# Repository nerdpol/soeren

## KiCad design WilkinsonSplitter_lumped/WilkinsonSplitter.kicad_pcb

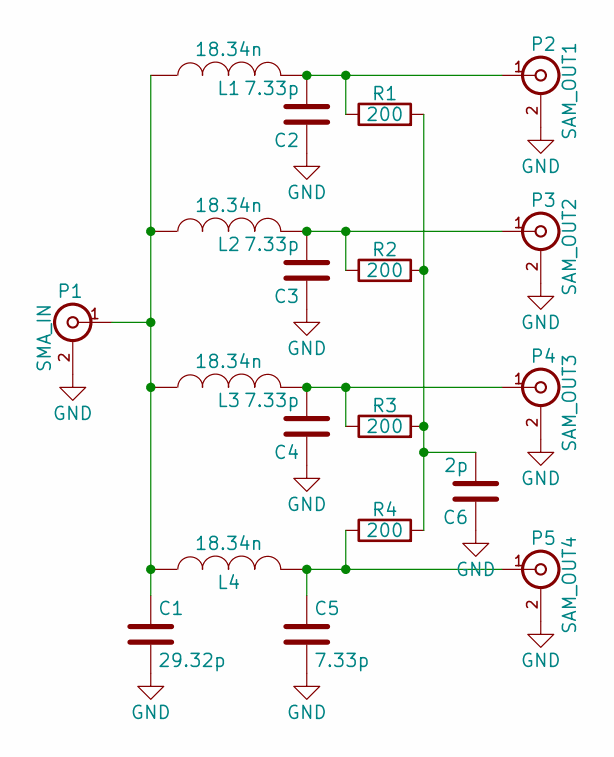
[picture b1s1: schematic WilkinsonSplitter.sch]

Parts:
C1: 29.32p; C_0402
C2, C3, C4, C5: 7.33p; C_0402
C6: 2p; C_0402
L1, L2, L3, L4: 18.34n; C_0402
P1: SMA_IN; Molex_SMA_Jack_Edge_Mount
P2: SAM_OUT1; Molex_SMA_Jack_Edge_Mount
P3: SAM_OUT2; Molex_SMA_Jack_Edge_Mount
P4: SAM_OUT3; Molex_SMA_Jack_Edge_Mount
P5: SAM_OUT4; Molex_SMA_Jack_Edge_Mount
R1, R2, R3, R4: 200; R_0402

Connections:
GND: C1.2, C2.1, C3.1, C4.1, C5.2, C6.1, P1.2 (Ext), P2.2 (Ext), P3.2 (Ext), P4.2 (Ext), P5.2 (Ext)
unnamed: C1.1, L1.1, L2.1, L3.1, L4.1, P1.1 (In)
unnamed: C2.2, L1.2, P2.1 (In), R1.1
unnamed: C3.2, L2.2, P3.1 (In), R2.1
unnamed: C4.2, L3.2, P4.1 (In), R3.1
unnamed: C5.1, L4.2, P5.1 (In), R4.1
unnamed: C6.2, R1.2, R2.2, R3.2, R4.2

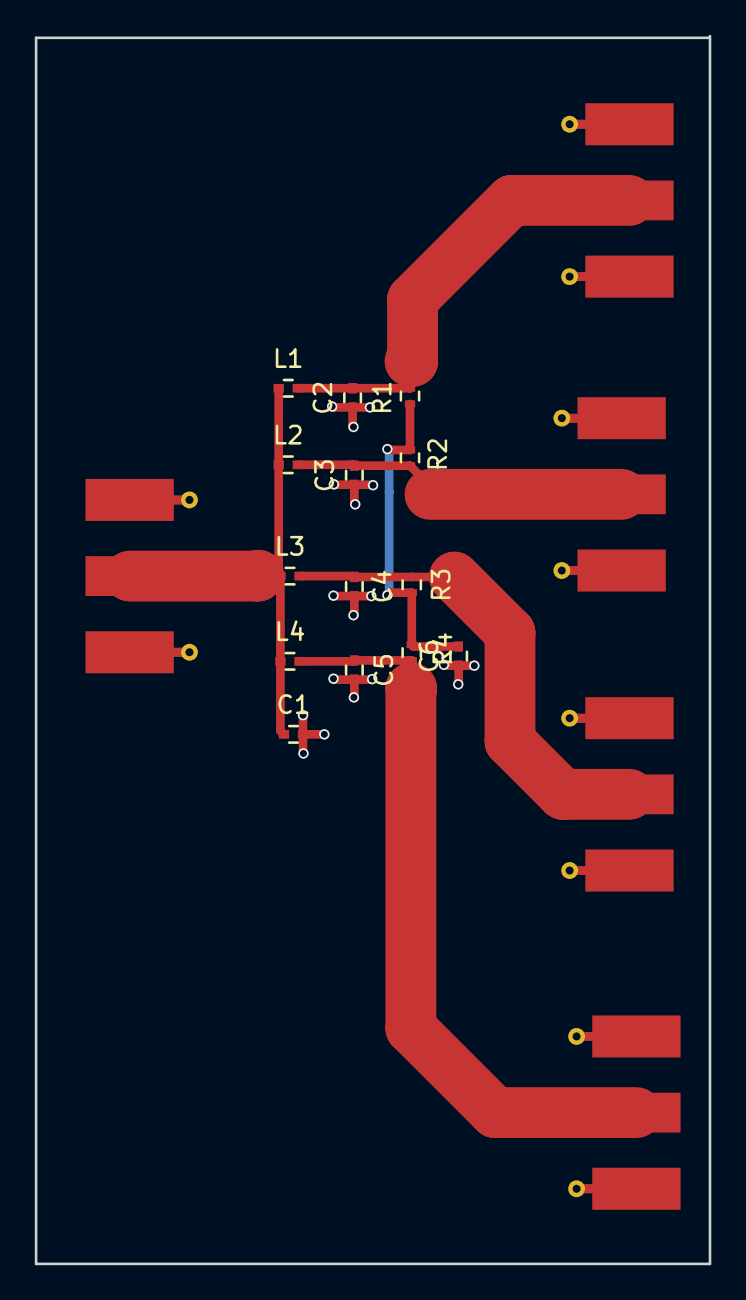
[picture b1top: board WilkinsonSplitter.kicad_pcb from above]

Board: 2 copper layers, 38.7 x 70.6 mm, 19 parts (0 on the bottom side), 7 nets.

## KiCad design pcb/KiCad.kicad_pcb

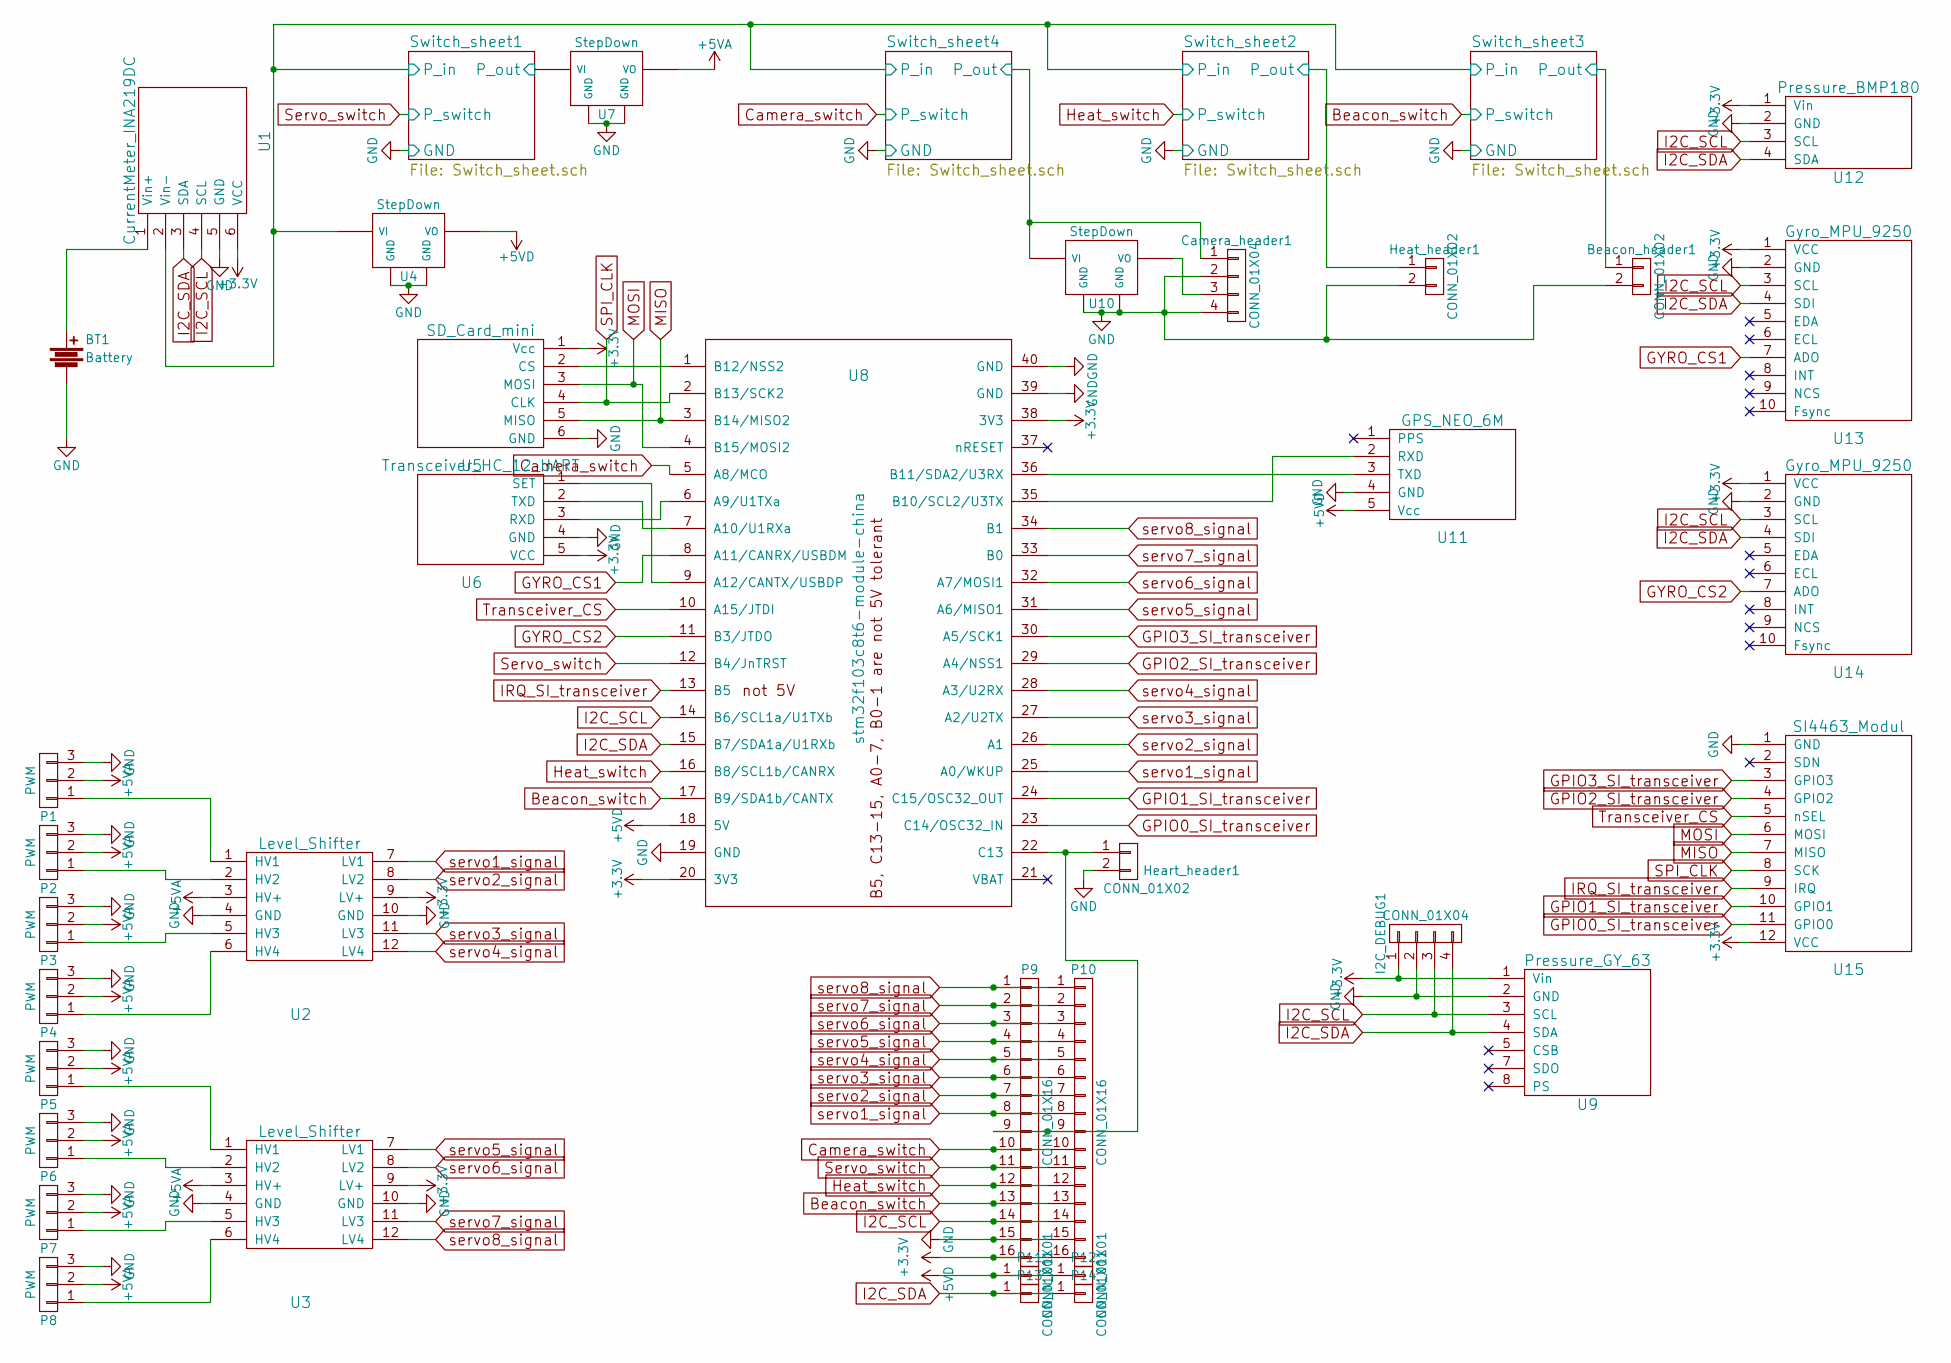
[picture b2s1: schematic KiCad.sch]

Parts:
BT1: Battery; Hirose_DF63-2P-3.96DSA_02x3.96mm_Straight
Beacon_header1: CONN_01X02; Molex_SPOX-5267_22-03-5025_02x2.54mm_Straight
Camera_header1: CONN_01X04; Molex_KK-6410-04_04x2.54mm_Straight
Heart_header1: CONN_01X02; Molex_KK-6410-02_02x2.54mm_Straight
Heat_header1: CONN_01X02; Molex_KK-6410-02_02x2.54mm_Straight
I2C_DEBUG1: CONN_01X04; Molex_KK-6410-04_04x2.54mm_Straight
P1, P2, P3, P4, P5, P6, P7, P8: PWM; Molex_KK-6410-03_03x2.54mm_Straight
P9, P10: CONN_01X16; Molex_PicoBlade_53261-1771_17x1.25mm_Angled
P11, P12, P13, P14: CONN_01X01; SL-101-X-XX_1x01
U1: CurrentMeter_INA219DC; Current_Sensor
U2, U3: Level_Shifter; level_shifter
U4, U7, U10: StepDown; step_down
U5: SD_Card_mini; SD-CARD
U6: Transceiver_HC_12_UART; HC-12
U8: stm32f103c8t6-module-china
U9: Pressure_GY_63; GY_63
U11: GPS_NEO_6M; GPS_Modul
U12: Pressure_BMP180; BMP180
U13, U14: Gyro_MPU_9250; MPU_9250
U15: SI4463_Modul

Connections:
+3V3: I2C_DEBUG1.1, P9.16, P10.16, U1.6 (VCC), U2.9 (LV+), U3.9 (LV+), U5.1 (Vcc), U6.5 (VCC), U8.20 (3V3), U8.38 (3V3), U9.1 (Vin), U12.1 (Vin), U13.1 (VCC), U14.1 (VCC), U15.12 (VCC)
+5VA: P1.2, P2.2, P3.2, P4.2, P5.2, P6.2, P7.2, P8.2, U2.3 (HV+), U3.3 (HV+), U7.3 (VO)
+5VD: P11.1, P12.1, U4.3 (VO), U8.18 (5V), U11.5 (Vcc)
/Switch_sheet1/P_in: U1.2 (Vin-), U4.1 (VI); also elsewhere on the board
/Switch_sheet1/P_out: U7.1 (VI); also elsewhere on the board
/Switch_sheet2/P_out: Heat_header1.1; also elsewhere on the board
/Switch_sheet3/P_out: Beacon_header1.1; also elsewhere on the board
/Switch_sheet4/P_out: Camera_header1.1, U10.1 (VI); also elsewhere on the board
Beacon_switch: P9.13, P10.13, U8.17 (B9/SDA1b/CANTX); also elsewhere on the board
Camera_switch: P9.10, P10.10, U8.5 (A8/MCO); also elsewhere on the board
GND: BT1.2, Beacon_header1.2, Camera_header1.2, Camera_header1.4, Heart_header1.2, Heat_header1.2, I2C_DEBUG1.2, P1.3, P2.3, P3.3, P4.3, P5.3, P6.3, P7.3, P8.3, P9.15, P10.15, U1.5 (GND), U2.4 (GND), U2.10 (GND), U3.4 (GND), U3.10 (GND), U4.2 (GND), U4.4 (GND), U5.6 (GND), U6.4 (GND), U7.2 (GND), U7.4 (GND), U8.19 (GND), U8.39 (GND), U8.40 (GND), U9.2 (GND), U10.2 (GND), U10.4 (GND), U11.4 (GND), U12.2 (GND), U13.2 (GND), U14.2 (GND), U15.1 (GND); also elsewhere on the board
GPIO0_SI_transceiver: U8.23 (C14/OSC32_IN), U15.11 (GPIO0)
GPIO1_SI_transceiver: U8.24 (C15/OSC32_OUT), U15.10 (GPIO1)
GPIO2_SI_transceiver: U8.29 (A4/NSS1), U15.4 (GPIO2)
GPIO3_SI_transceiver: U8.30 (A5/SCK1), U15.3 (GPIO3)
GYRO_CS1: U8.8 (A11/CANRX/USBDM), U13.7 (ADO)
GYRO_CS2: U8.11 (B3/JTDO), U14.7 (ADO)
Heat_switch: P9.12, P10.12, U8.16 (B8/SCL1b/CANRX); also elsewhere on the board
I2C_SCL: I2C_DEBUG1.3, P9.14, P10.14, U1.4 (SCL), U8.14 (B6/SCL1a/U1TXb), U9.3 (SCL), U12.3 (SCL), U13.3 (SCL), U14.3 (SCL)
I2C_SDA: I2C_DEBUG1.4, P13.1, P14.1, U1.3 (SDA), U8.15 (B7/SDA1a/U1RXb), U9.4 (SDA), U12.4 (SDA), U13.4 (SDI), U14.4 (SDI)
IRQ_SI_transceiver: U8.13 (B5), U15.9 (IRQ)
MISO: U5.5 (MISO), U8.3 (B14/MISO2), U15.7 (MISO)
MOSI: U5.3 (MOSI), U8.4 (B15/MOSI2), U15.6 (MOSI)
unnamed: BT1.1, U1.1 (Vin+)
unnamed: Camera_header1.3, U10.3 (VO)
unnamed: Heart_header1.1, P9.9, P10.9, U8.22 (C13)
unnamed: P1.1, U2.1 (HV1)
unnamed: P2.1, U2.2 (HV2)
unnamed: P3.1, U2.5 (HV3)
unnamed: P4.1, U2.6 (HV4)
unnamed: P5.1, U3.1 (HV1)
unnamed: P6.1, U3.2 (HV2)
unnamed: P7.1, U3.5 (HV3)
unnamed: P8.1, U3.6 (HV4)
unnamed: U5.2 (CS), U8.1 (B12/NSS2)
unnamed: U6.1 (SET), U8.9 (A12/CANTX/USBDP)
unnamed: U6.2 (TXD), U8.7 (A10/U1RXa)
unnamed: U6.3 (RXD), U8.6 (A9/U1TXa)
unnamed: U8.35 (B10/SCL2/U3TX), U11.2 (RXD)
unnamed: U8.36 (B11/SDA2/U3RX), U11.3 (TXD)
SPI_CLK: U5.4 (CLK), U8.2 (B13/SCK2), U15.8 (SCK)
Servo_switch: P9.11, P10.11, U8.12 (B4/JnTRST); also elsewhere on the board
Transceiver_CS: U8.10 (A15/JTDI), U15.5 (nSEL)
servo1_signal: P9.8, P10.8, U2.7 (LV1), U8.25 (A0/WKUP)
servo2_signal: P9.7, P10.7, U2.8 (LV2), U8.26 (A1)
servo3_signal: P9.6, P10.6, U2.11 (LV3), U8.27 (A2/U2TX)
servo4_signal: P9.5, P10.5, U2.12 (LV4), U8.28 (A3/U2RX)
servo5_signal: P9.4, P10.4, U3.7 (LV1), U8.31 (A6/MISO1)
servo6_signal: P9.3, P10.3, U3.8 (LV2), U8.32 (A7/MOSI1)
servo7_signal: P9.2, P10.2, U3.11 (LV3), U8.33 (B0)
servo8_signal: P9.1, P10.1, U3.12 (LV4), U8.34 (B1)

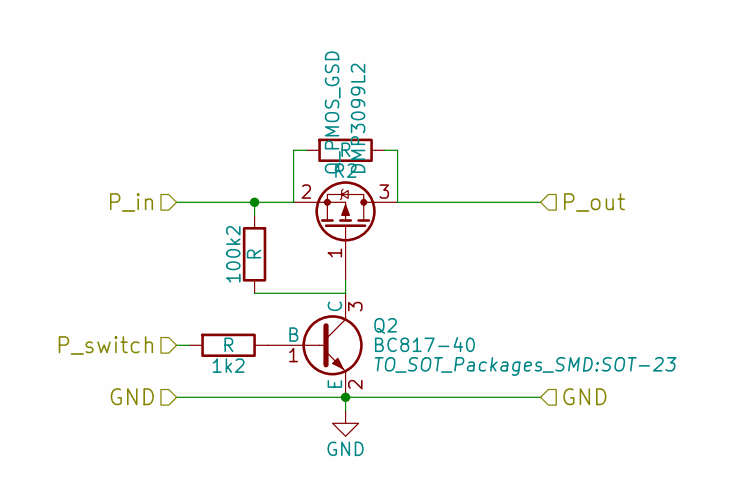
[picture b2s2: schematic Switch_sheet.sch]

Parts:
1k1, 100k1: R; R_0603_HandSoldering
DMP3099L1: Q_PMOS_GSD; SOT-23-5_HandSoldering
Q1: BC817-40; SOT-23
R1: R; R_0603_HandSoldering

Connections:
/Switch_sheet1/P_in: 100k1.2, DMP3099L1.2 (S), R1.2; also elsewhere on the board
/Switch_sheet1/P_out: DMP3099L1.3 (D), R1.1; also elsewhere on the board
GND: Q1.2 (E); also elsewhere on the board
unnamed: 1k1.1, Q1.1 (B)
unnamed: 100k1.1, DMP3099L1.1 (G), Q1.3 (C)
Servo_switch: 1k1.2; also elsewhere on the board

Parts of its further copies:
1k2, 1k3, 1k4, 100k2, 100k3, 100k4: R; R_0603_HandSoldering
DMP3099L2, DMP3099L3, DMP3099L4: Q_PMOS_GSD; SOT-23-5_HandSoldering
Q2, Q3, Q4: BC817-40; SOT-23
R2, R3, R4: R; R_0603_HandSoldering

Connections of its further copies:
/Switch_sheet1/P_in: 100k2.2, 100k3.2, 100k4.2, DMP3099L2.2 (S), DMP3099L3.2 (S), DMP3099L4.2 (S), R2.2, R3.2, R4.2; also elsewhere on the board
/Switch_sheet2/P_out: DMP3099L3.3 (D), R3.1; also elsewhere on the board
/Switch_sheet3/P_out: DMP3099L4.3 (D), R4.1; also elsewhere on the board
/Switch_sheet4/P_out: DMP3099L2.3 (D), R2.1; also elsewhere on the board
Beacon_switch: 1k4.2; also elsewhere on the board
Camera_switch: 1k2.2; also elsewhere on the board
GND: Q2.2 (E), Q3.2 (E), Q4.2 (E); also elsewhere on the board
Heat_switch: 1k3.2; also elsewhere on the board
unnamed: 1k2.1, Q2.1 (B)
unnamed: 1k3.1, Q3.1 (B)
unnamed: 1k4.1, Q4.1 (B)
unnamed: 100k2.1, DMP3099L2.1 (G), Q2.3 (C)
unnamed: 100k3.1, DMP3099L3.1 (G), Q3.3 (C)
unnamed: 100k4.1, DMP3099L4.1 (G), Q4.3 (C)

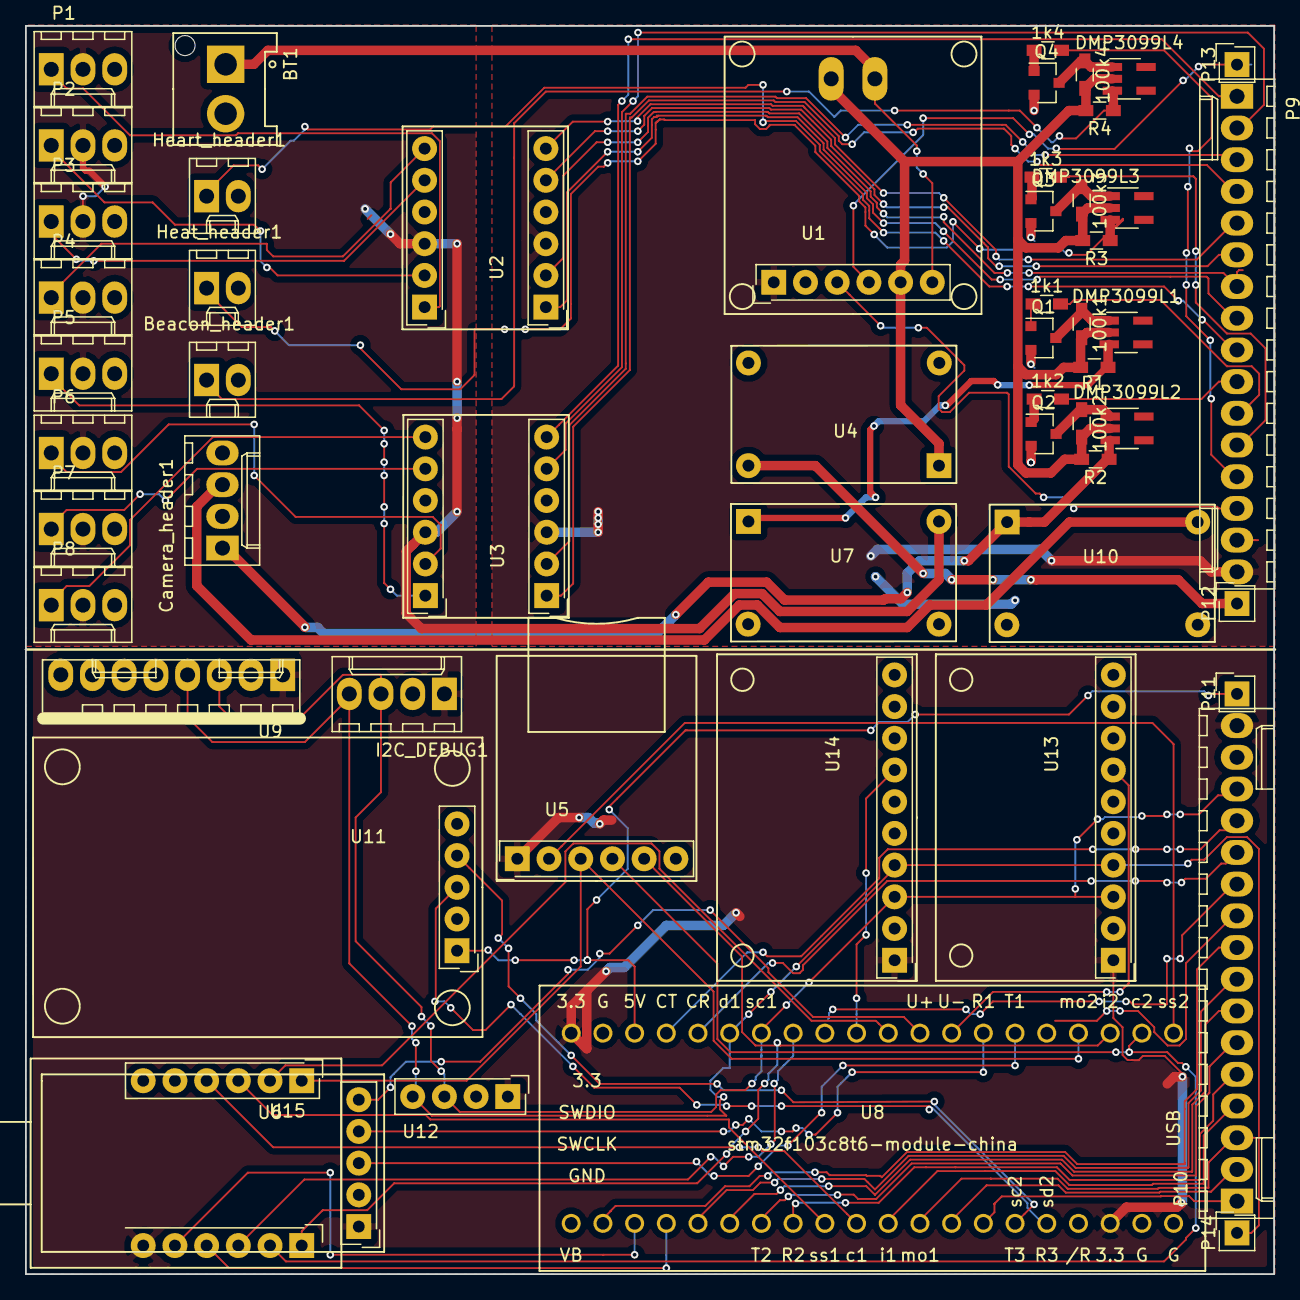
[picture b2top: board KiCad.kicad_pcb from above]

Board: 2 copper layers, 100.0 x 100.0 mm, 55 parts (0 on the bottom side), 59 nets.

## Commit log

2017-03-27 init
2017-03-27 irgend welche werte verändert
2017-04-03 FlightController
2017-04-03 Flightcontroller working!
2017-05-01 Parser working
2017-05-22 Port to STM32
2017-05-29 New stuff
2017-08-07 Reorganize
2017-08-07 Add joystick
2017-08-14 Add small test program for the INA219 power sensor
2017-08-14 Fix i2c scan
2017-08-14 Fix some telemetry packets
2017-08-15 Add telemetry reader and joystick/HC12 test scripts
2017-08-28 Add command line option fpr joystick sine period
2017-09-04 refactor
2017-09-11 Major refactor.
2017-09-18 sensor data fusion running on stm32, mag call missing
2017-09-20 Matlab compass calibration
2017-09-20 compass correction submit von Matlab?
2017-09-22 Add files via upload
    Run in processing enviroment
    -> adjust COM Port
    // NOTE: requires ToxicLibs to be installed in order to run properly.
    // 1. Download from http://toxiclibs.org/downloads
    // 2. Extract into [userdir]/Processing/libraries
    // (location may be different on Mac/Linux)
2017-09-22 Data Visualisation using Processing
2017-09-22 kleine Aenderung
2017-09-22 teapot.pde in Ordner verschoben
2017-09-22 Prepare Data Fusion example code to get fused with flight controler in here
2017-09-22 Portexpander und i2c adc getestet!
2017-09-22 datasheet
2017-09-25 FlightUmgebungTest an Franz seine Routine anpassen. NOch fehlerbei deklaration von quaternionen
2017-09-25 + control_hud erste Schritte
2017-09-25 Bat PCB nearly done
2017-09-25 some new code -> bat management
2017-09-26 * control_hud Künstlicher Horizont Entwurf
2017-09-26 * control_hud python 3
2017-09-27 * control_hud more painting
2017-10-02 weitere PCB Module
2017-10-02 * control_hud test real sensor
2017-10-02 * control_hud refactor, argparse
2017-10-07 * control_hud angle indicator update
2017-10-16 pca9685 PWM
2017-10-16 + udp prototype impl
2017-10-16 Alles was noetig ist
2017-10-23 * artificial horizon finish
2017-10-23 Servo not worling!
2017-10-30 * hud: speed & height
2017-11-06 Add PWM Servos
2017-11-06 added manual_controll beginning
2017-11-06 Wilkinson Splitter fuer 4xHC12 hinzugefuegt
2017-11-06 added joystick in manual controll
2017-11-06 * control_hud: diagram
2017-11-09 added control_hud concept drawing
2017-11-13 * control_hud: use time as x-axis
2017-11-20 leave me alone
2017-11-20 * protocol: add units
2017-11-20 SOIC-8 Footprint hinzugefuegt
2017-11-20 Ruder acuh
2017-11-20 Neue Footprints by Soeren
2017-11-20 added test files
2017-11-27 Battery Management
2017-11-27 Update Protocol and Mux; Add Heartbeat Program
2018-01-23 * start writing UdpReceiver library
2018-01-24 + udp receiver library
2018-01-29 + Regler
2018-01-29 + control_map
2018-02-05 reglerparameteranpassung
2018-02-05 * map works, udp json parsing still fails
2018-02-12 * map: udp working
